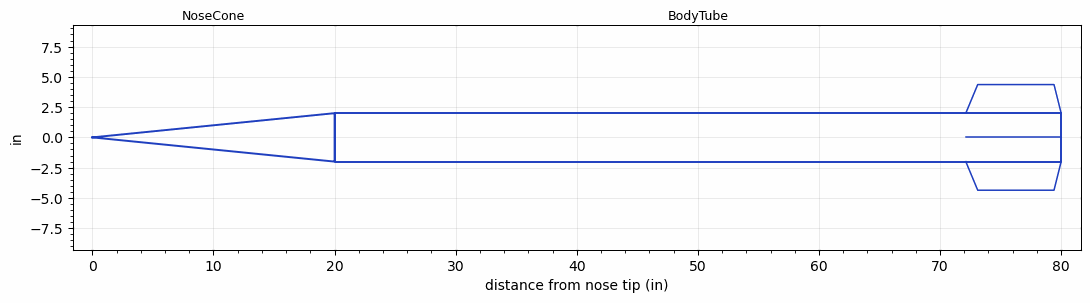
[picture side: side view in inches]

<RASAeroDocument>
 <FileVersion>2</FileVersion>
 <RocketDesign>
  <NoseCone>
   <Length>20</Length>
   <Diameter>4</Diameter>
   <Shape>Conical</Shape>
   <Location>0</Location>
  </NoseCone>
  <BodyTube>
   <Length>60</Length>
   <Diameter>4</Diameter>
   <Location>20</Location>
   <Fin>
    <Count>4</Count>
    <Chord>7.874</Chord>
    <Span>2.3622</Span>
    <SweepDistance>0.9843</SweepDistance>
    <TipChord>6.2992</TipChord>
    <Thickness>0.3937</Thickness>
    <Location>7.874</Location>
    <AirfoilSection>Hexagonal</AirfoilSection>
    <FX1>1</FX1>
    <FX3>1</FX3>
   </Fin>
  </BodyTube>
  <Surface>Smooth Paint</Surface>
  <ModifiedBarrowman>True</ModifiedBarrowman>
  <Turbulence>True</Turbulence>
  <UseBooster1>False</UseBooster1>
  <UseBooster2>False</UseBooster2>
 </RocketDesign>
 <LaunchSite>
  <Altitude>2000</Altitude>
  <Pressure>0</Pressure>
  <RodAngle>0</RodAngle>
  <RodLength>20</RodLength>
  <Temperature>50</Temperature>
  <WindSpeed>0</WindSpeed>
 </LaunchSite>
 <Recovery>
  <Altitude1>1000</Altitude1>
  <Altitude2>1000</Altitude2>
  <DeviceType1>None</DeviceType1>
  <DeviceType2>None</DeviceType2>
  <Event1>False</Event1>
  <Event2>False</Event2>
  <Size1>1</Size1>
  <Size2>1</Size2>
  <EventType1>None</EventType1>
  <EventType2>None</EventType2>
  <CD1>1.33</CD1>
  <CD2>1.33</CD2>
 </Recovery>
 <SimulationList>
  <Simulation>
   <SustainerEngine>O5280X  (AT)</SustainerEngine>
   <SustainerLaunchWt>44.5</SustainerLaunchWt>
   <SustainerNozzleDiameter>3</SustainerNozzleDiameter>
   <SustainerCG>47.53</SustainerCG>
   <SustainerIgnitionDelay>0</SustainerIgnitionDelay>
   <Booster1SeparationDelay>0</Booster1SeparationDelay>
   <Booster1IgnitionDelay>0</Booster1IgnitionDelay>
   <IncludeBooster1>False</IncludeBooster1>
   <Booster2Delay>0</Booster2Delay>
   <IncludeBooster2>False</IncludeBooster2>
  </Simulation>
  <Simulation>
   <SustainerEngine>N5800-CS  (CTI)</SustainerEngine>
   <SustainerLaunchWt>42.6</SustainerLaunchWt>
   <SustainerNozzleDiameter>3</SustainerNozzleDiameter>
   <SustainerCG>51.33</SustainerCG>
   <SustainerIgnitionDelay>0</SustainerIgnitionDelay>
   <Booster1SeparationDelay>0</Booster1SeparationDelay>
   <Booster1IgnitionDelay>0</Booster1IgnitionDelay>
   <IncludeBooster1>False</IncludeBooster1>
   <Booster2Delay>0</Booster2Delay>
   <IncludeBooster2>False</IncludeBooster2>
   <TimetoApogee>49.35772</TimetoApogee>
   <MaxAltitude>56092.21</MaxAltitude>
   <MaxVelocity>3987.045</MaxVelocity>
  </Simulation>
 </SimulationList>
</RASAeroDocument>
